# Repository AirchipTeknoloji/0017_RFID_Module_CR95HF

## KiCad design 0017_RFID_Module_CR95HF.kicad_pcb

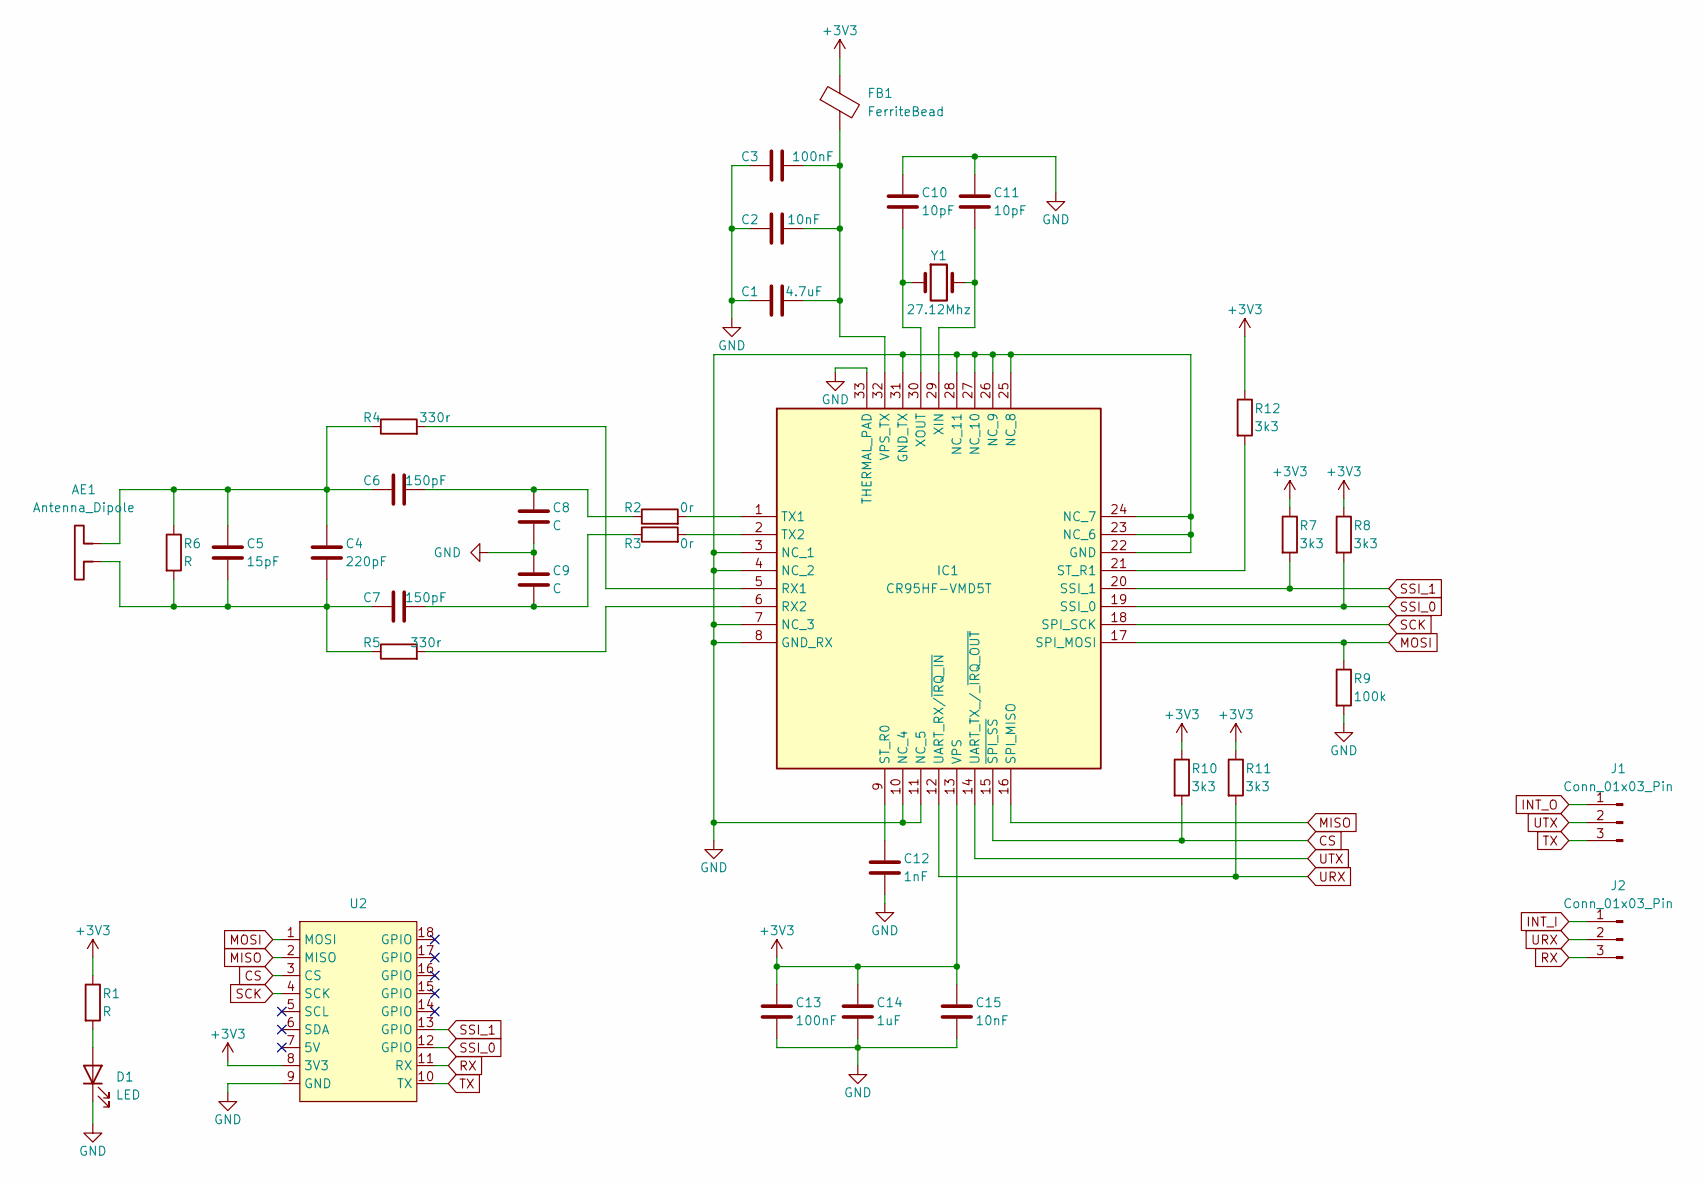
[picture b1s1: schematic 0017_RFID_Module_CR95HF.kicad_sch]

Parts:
AE1: Antenna_Dipole
C1: 4.7uF; C_0603_1608Metric
C2, C15: 10nF; C_0603_1608Metric
C3, C13: 100nF; C_0603_1608Metric
C4: 220pF; C_0603_1608Metric
C5: 15pF; C_0603_1608Metric
C6, C7: 150pF; C_0603_1608Metric
C8, C9: C; C_0603_1608Metric
C10, C11: 10pF; C_0603_1608Metric
C12: 1nF; C_0603_1608Metric
C14: 1uF; C_0603_1608Metric
D1: LED; LED_0603_1608Metric
FB1: FerriteBead; L_0603_1608Metric
IC1: CR95HF-VMD5T; QFN50P500X500X100-33N-D; Mouser Part Number 511-CR95HF-VMD5T
J1, J2: Conn_01x03_Pin; SolderJumper-3_P1.3mm_Open_Pad1.0x1.5mm
R1, R6: R; R_0603_1608Metric
R2, R3: 0r; R_0603_1608Metric
R4, R5: 330r; R_0603_1608Metric
R7, R8, R10, R11, R12: 3k3; R_0603_1608Metric
R9: 100k; R_0603_1608Metric
U2: air__module
Y1: 27.12Mhz; Crystal_SMD_5032-2Pin_5.0x3.2mm

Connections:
+3V3: C13.1, C14.1, C15.1, FB1.1, IC1.13 (VPS), R1.1, R7.1, R8.1, R10.1, R11.1, R12.1, U2.8 (3V3)
CS: IC1.15 (~SPI_SS), R10.2, U2.3 (CS)
GND: C1.1, C2.1, C3.1, C8.2, C9.1, C10.1, C11.1, C12.2, C13.2, C14.2, C15.2, D1.1 (K), IC1.3 (NC_1), IC1.4 (NC_2), IC1.7 (NC_3), IC1.8 (GND_RX), IC1.10 (NC_4), IC1.11 (NC_5), IC1.22 (GND), IC1.23 (NC_6), IC1.24 (NC_7), IC1.25 (NC_8), IC1.26 (NC_9), IC1.27 (NC_10), IC1.28 (NC_11), IC1.31 (GND_TX), IC1.33 (THERMAL_PAD), R9.2, U2.9 (GND)
INT_I: J2.1
INT_O: J1.1
MISO: IC1.16 (SPI_MISO), U2.2 (MISO)
MOSI: IC1.17 (SPI_MOSI), R9.1, U2.1 (MOSI)
unnamed: AE1.1, C4.2, C5.2, C7.1, R5.1, R6.2
unnamed: AE1.2, C4.1, C5.1, C6.1, R4.1, R6.1
unnamed: C6.2, C8.1, R2.1
unnamed: C7.2, C9.2, R3.1
unnamed: D1.2 (A), R1.2
unnamed: IC1.5 (RX1), R4.2
unnamed: IC1.6 (RX2), R5.2
unnamed: C12.1, IC1.9 (ST_R0)
unnamed: IC1.21 (ST_R1), R12.2
unnamed: IC1.1 (TX1), R2.2
unnamed: IC1.2 (TX2), R3.2
unnamed: C1.2, C2.2, C3.2, FB1.2, IC1.32 (VPS_TX)
unnamed: C11.2, IC1.29 (XIN), Y1.2
unnamed: C10.2, IC1.30 (XOUT), Y1.1
RX: J2.3, U2.11 (RX)
SCK: IC1.18 (SPI_SCK), U2.4 (SCK)
SSI_0: IC1.19 (SSI_0), R8.2, U2.12 (GPIO)
SSI_1: IC1.20 (SSI_1), R7.2, U2.13 (GPIO)
TX: J1.3, U2.10 (TX)
URX: IC1.12 (UART_RX/~IRQ_IN), J2.2, R11.2
UTX: IC1.14 (UART_TX_/_~IRQ_OUT), J1.2

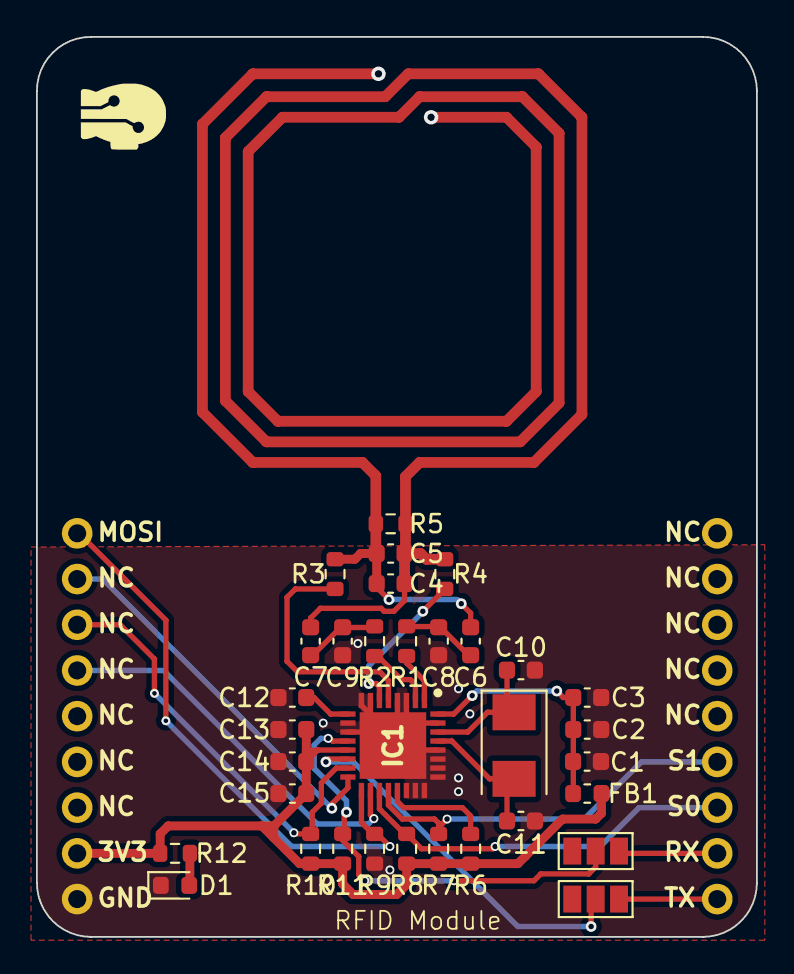
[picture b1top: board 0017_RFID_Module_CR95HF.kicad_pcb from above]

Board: 2 copper layers, 40.0 x 50.0 mm, 34 parts (0 on the bottom side), 26 nets.
